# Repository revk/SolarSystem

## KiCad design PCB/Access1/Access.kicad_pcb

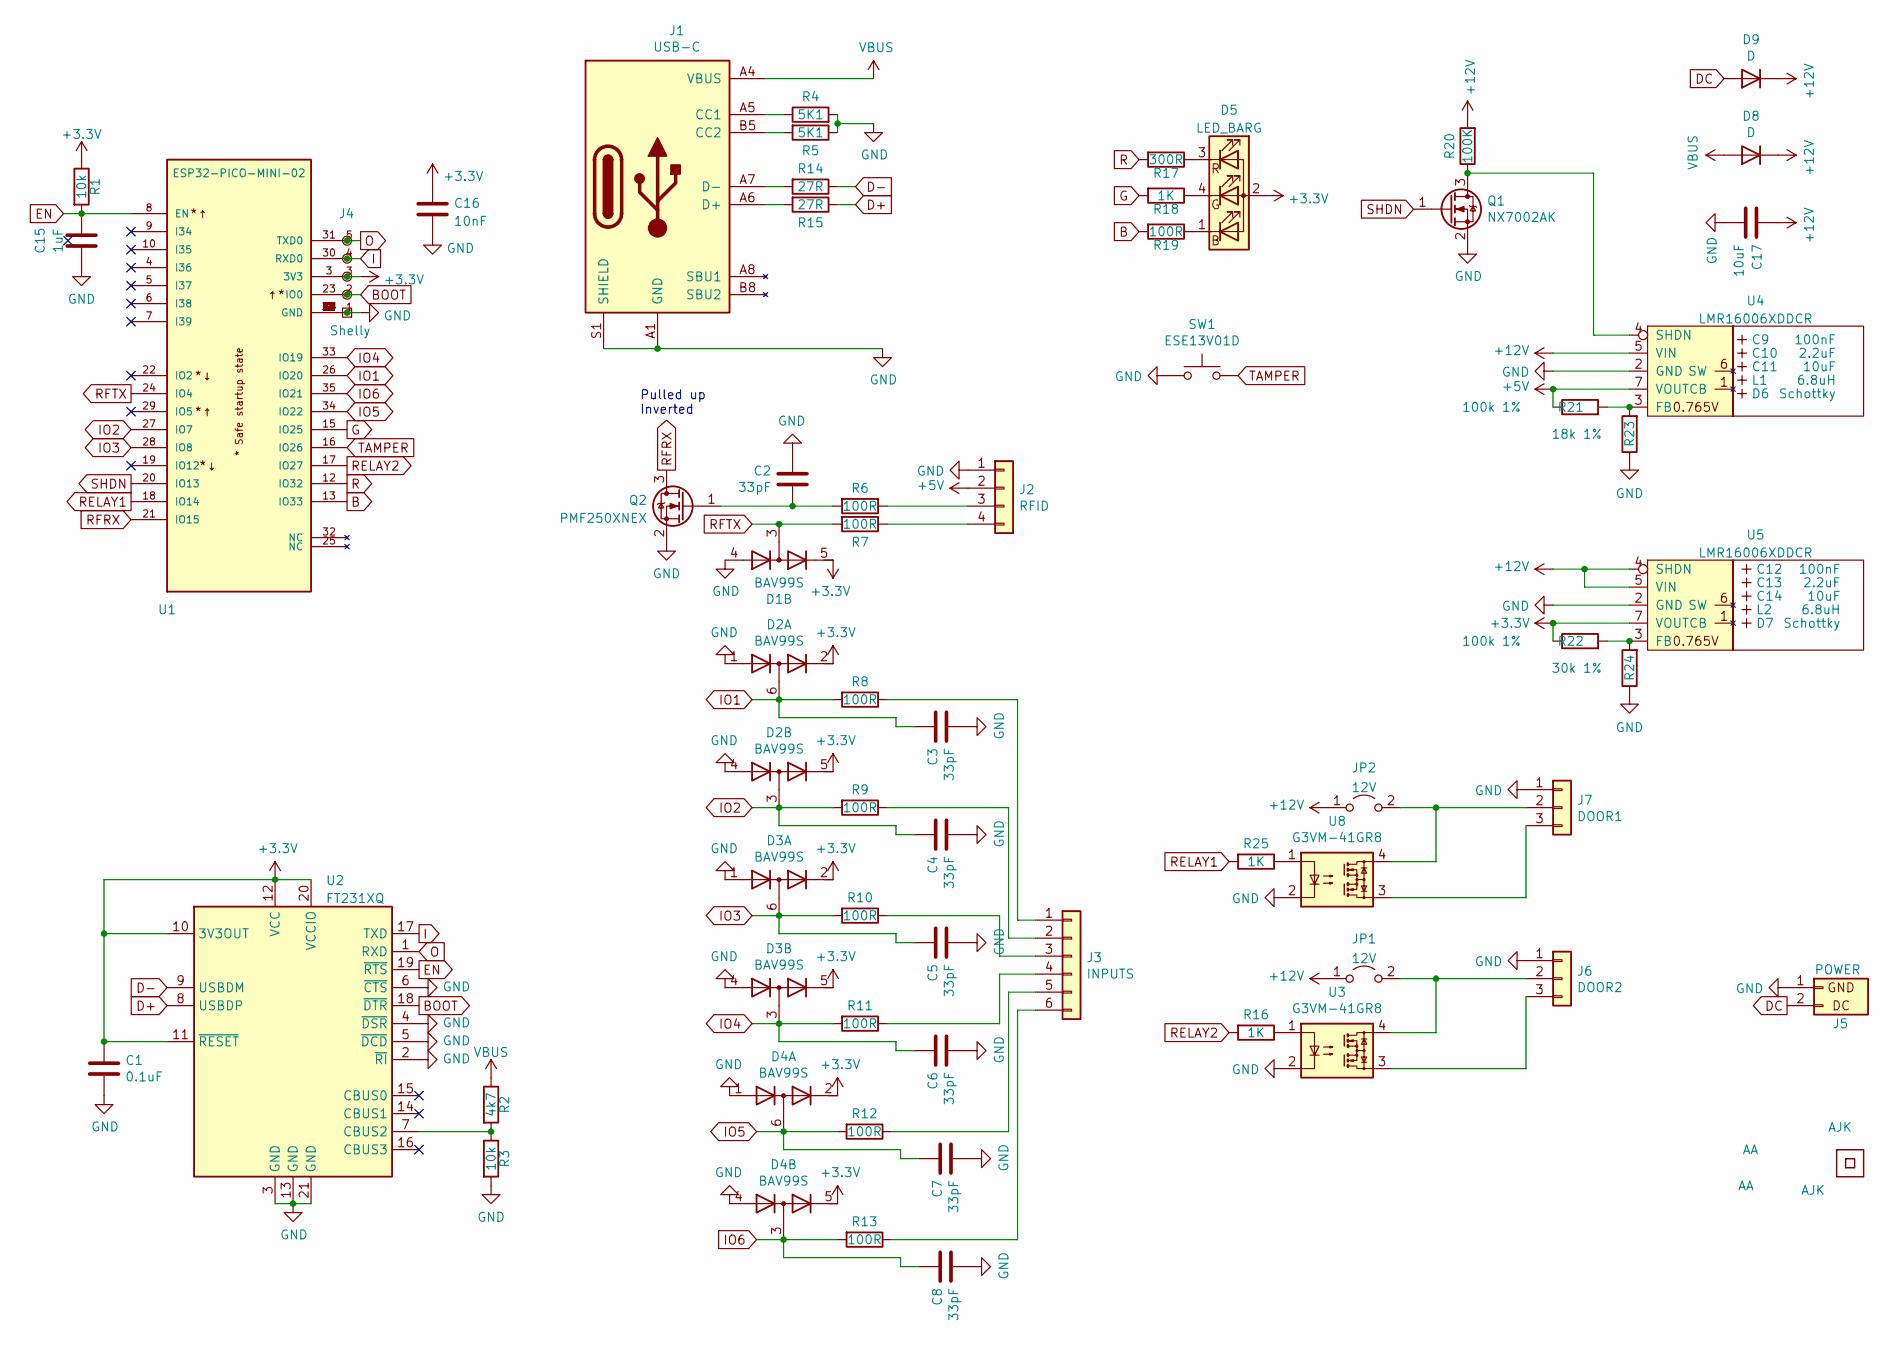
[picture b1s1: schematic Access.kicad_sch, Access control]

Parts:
AJK1: AJK
C1: 0.1uF; C_0603
C2, C3, C4, C5, C6, C7, C8: 33pF; C_0603
C9, C12: 100nF; C_0603_; LCSC Part # C30926
C10, C13: 2.2uF; C_0805_; LCSC Part # C19110
C11, C14: 10uF; C_0805_; LCSC Part # C17024
C15: 1uF; C_0603
C16: 10nF; C_0603
C17: 10uF; C_0805
D1, D2, D3, D4: BAV99S; SOT-363_SC-70-6; JLCPCB Rotation Offset 90
D5: LED_BARG; MHS190RGBCT; LCSC Part # C409798
D6, D7: Schottky; D_1206_; LCSC Part # C143805
D8, D9: D; D_1206; LCSC Part # C143805
J1: USB-C; USC16-TR; LCSC Part # C709357
J2: RFID; PTSM-HH-4-RA
J3: INPUTS; PTSM-HH-6-RA
J4: Shelly
J5: POWER; PTSM-HH1-2-RA
J6: DOOR2; PTSM-HH1-3-RA-W
J7: DOOR1; PTSM-HH1-3-RA
JP1, JP2: 12V; SolderJumper-2_P1.3mm_Open_RoundedPad1.0x1.5mm
L1, L2: 6.8uH; L_4x4_; LCSC Part # C354575
Logo1: AJK
Q1: NX7002AK; SOT-23; Part No NX7002AK; JLCPCB Rotation Offset 180
Q2: PMF250XNEX; SOT-323_SC-70; Part No PMF250XNEX; LCSC Part # C504047
R1, R3: 10k; R_0603
R2: 4k7; R_0603
R4, R5: 5K1; R_0603
R6, R7, R8, R9, R10, R11, R12, R13: 100R; R_0603
R14, R15: 27R; R_0603
R16, R25: 1K; R_0603
R17: 300R; R_0603; Part No 0603-680R
R18: 1K; R_0603; Part No 0603-2K
R19: 100R; R_0603; Part No 0603-220R
R20: 100K; R_0603
R21, R22: 100k 1%; R_0603; LCSC Part # C14675
R23: 18k 1%; R_0603; LCSC Part # C114610
R24: 30k 1%; R_0603; LCSC Part # C100001
SW1: ESE13V01D; ESE13
U1: ESP32-PICO-MINI-02; PARTREV v1.0; LCSC Part # C2980306
U2: FT231XQ; QFN-20-1EP_4x4mm_P0.5mm_EP2.5x2.5mm; JLCPCB Rotation Offset -90
U3, U8: G3VM-41GR8; Special-SOP-4-3.7x4.55; LCSC Part # C2691601
U4, U5: LMR16006XDDCR; SOT-23-Thin-6-Reg; Part No LMR16006XDDCR; LCSC Part # C87080
U6, U9: AA
U7: QR; QR-SS

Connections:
+3.3V: C1.1, C16.1, D1.5 (K4), D2.2 (K2), D2.5 (K4), D3.2 (K2), D3.5 (K4), D4.2 (K2), D4.5 (K4), D5.2 (A), J4.3 (3V3), R1.1, R22.1, U1.3 (3V3), U2.10 (3V3OUT), U2.11 (~RESET), U2.12 (VCC), U2.20 (VCCIO), U5.7 (VOUT)
+5V: J2.2, R21.1, U4.7 (VOUT)
+12V: C17.1, D8.1 (K), D9.1 (K), JP1.1 (A), JP2.1 (A), R20.2, U4.5 (VIN), U5.4 (SHDN), U5.5 (VIN)
B: R19.2, U1.13 (IO33)
BOOT: J4.2 (0), U1.23 (IO0), U2.18 (~DTR)
D+: R15.1, U2.8 (USBDP)
D-: R14.1, U2.9 (USBDM)
DC: D9.2 (A), J5.2 (DC)
EN: C15.2, R1.2, U1.8 (EN), U2.19 (~RTS)
G: R18.2, U1.15 (IO25)
GND: C1.2, C2.1, C3.2, C4.2, C5.2, C6.2, C7.2, C8.2, C15.1, C16.2, C17.2, D1.4 (A3), D2.1 (A1), D2.4 (A3), D3.1 (A1), D3.4 (A3), D4.1 (A1), D4.4 (A3), J1.A1 (GND), J1.A12 (GND), J1.B1 (GND), J1.B12 (GND), J1.S1 (SHIELD), J2.1, J4.1 (GND), J5.1 (GND), J6.1, J7.1, Q1.2 (S), Q2.2 (S), R3.2, R4.2, R5.1, R23.1, R24.1, SW1.1, U1.1 (GND), U1.2 (GND), U1.11 (GND), U1.14 (GND), U1.36 (GND), U1.37 (GND), U1.38 (GND), U1.39 (GND), U1.40 (GND), U1.41 (GND), U1.42 (GND), U1.43 (GND), U1.44 (GND), U1.45 (GND), U1.46 (GND), U1.47 (GND), U1.48 (GND), U1.49 (GND), U1.50 (GND), U1.51 (GND), U1.52 (GND), U1.53 (GND), U2.2 (~RI), U2.3 (GND), U2.4 (~DSR), U2.5 (~DCD), U2.6 (~CTS), U2.13 (GND), U2.21 (GND), U3.2, U4.2 (GND), U5.2 (GND), U8.2
I: J4.4 (Rx), U1.30 (RXD0), U2.17 (TXD)
IO1: C3.1, D2.6 (K3A4), R8.2, U1.26 (IO20)
IO2: C4.1, D2.3 (K1A2), R9.2, U1.27 (IO7)
IO3: C5.1, D3.6 (K3A4), R10.2, U1.28 (IO8)
IO4: C6.1, D3.3 (K1A2), R11.2, U1.33 (IO19)
IO5: C7.1, D4.6 (K3A4), R12.2, U1.34 (IO22)
IO6: C8.1, D4.3 (K1A2), R13.2, U1.35 (IO21)
unnamed: D5.1 (BK), R19.1
unnamed: D5.4 (GK), R18.1
unnamed: D5.3 (RK), R17.1
unnamed: J1.A5 (CC1), R4.1
unnamed: J1.B5 (CC2), R5.2
unnamed: J1.A6 (D+), J1.B6 (D+), R15.2
unnamed: J1.A7 (D-), J1.B7 (D-), R14.2
unnamed: J2.3, R6.1
unnamed: J2.4, R7.1
unnamed: J3.1, R8.1
unnamed: J3.2, R9.1
unnamed: J3.3, R10.1
unnamed: J3.4, R11.1
unnamed: J3.5, R12.1
unnamed: J3.6, R13.1
unnamed: J6.2, JP1.2 (B), U3.4
unnamed: J6.3, U3.3
unnamed: J7.2, JP2.2 (B), U8.4
unnamed: J7.3, U8.3
unnamed: Q1.3 (D), R20.1, U4.4 (SHDN)
unnamed: C2.2, Q2.1 (G), R6.2
unnamed: R16.1, U3.1
unnamed: R25.1, U8.1
unnamed: R2.2, R3.1, U2.7 (CBUS2)
unnamed: R21.2, R23.2, U4.3 (FB)
unnamed: R22.2, R24.2, U5.3 (FB)
O: J4.5 (Tx), U1.31 (TXD0), U2.1 (RXD)
R: R17.2, U1.12 (IO32)
RELAY1: R25.2, U1.18 (IO14)
RELAY2: R16.2, U1.17 (IO27)
RFRX: Q2.3 (D), U1.21 (IO15)
RFTX: D1.3 (K1A2), R7.2, U1.24 (IO4)
SHDN: Q1.1 (G), U1.20 (IO13)
TAMPER: SW1.2, U1.16 (IO26)
VBUS: D8.2 (A), J1.A4 (VBUS), J1.A9 (VBUS), J1.B4 (VBUS), J1.B9 (VBUS), R2.1

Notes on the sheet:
Pulled up Inverted

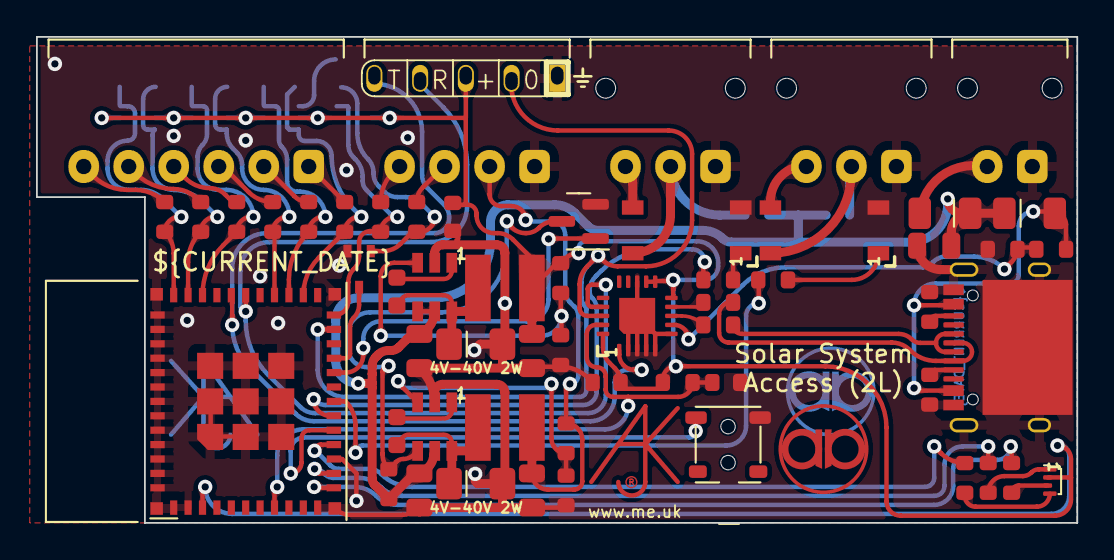
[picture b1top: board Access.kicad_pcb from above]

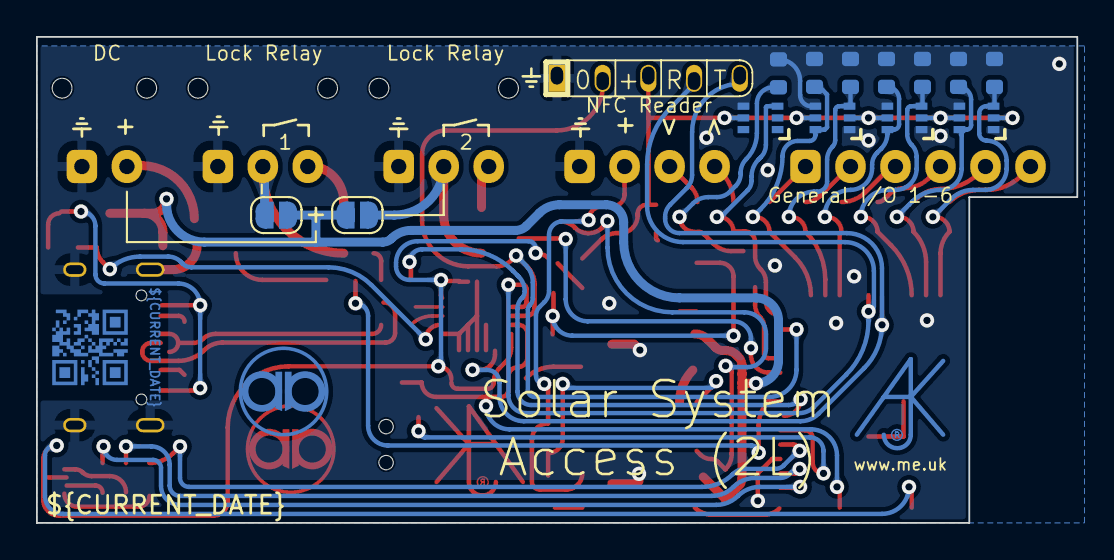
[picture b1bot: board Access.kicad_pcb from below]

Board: 2 copper layers, 57.8 x 27.0 mm, 76 parts (16 on the bottom side), 53 nets.

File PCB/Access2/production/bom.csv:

Designator,Footprint,Quantity,Value,LCSC Part #
C1,C_0603,1,0.1uF,
"C10, C13",C_0805_,2,2.2uF,C19110
"C11, C14",C_0805_,2,10uF,C17024
"C12, C9",C_0603_,2,100nF,C30926
"C15, C16",C_0603,2,10nF,
C17,C_0805,1,10uF,
"C2, C3, C4, C5, C6, C7, C8",C_0603,7,33pF,
"D1, D2, D3, D4",SOT-363_SC-70-6,4,BAV99S,
D5,MHS190RGBCT,1,LED_BARG,C409798
"D6, D7",D_1206_,2,Schottky,C143805
"D8, D9",D_1206,2,D,C143805
J1,USC16-TR,1,USB-C,C709357
J2,PTSM-HH-4-RA,1,RFID,
J3,PTSM-HH-6-RA,1,INPUTS,
J5,PTSM-HH1-2-RA,1,POWER,
J6,PTSM-HH1-3-RA,1,DOOR,
"L1, L2",L_4x4_,2,6.8uH,C354575
Q1,SOT-23,1,NX7002AK,
Q2,SOT-323_SC-70,1,PMF250XNEX,C504047
"R1, R3",R_0603,2,10k,
"R10, R11, R12, R13, R19, R6, R7, R8, R9",R_0603,9,100R,
"R14, R15",R_0603,2,27R,
"R16, R18",R_0603,2,1K,
R17,R_0603,1,300R,
R2,R_0603,1,4k7,
R20,R_0603,1,100K,
"R21, R22",R_0603,2,100k 1%,C14675
R23,R_0603,1,18k 1%,C114610
R24,R_0603,1,30k 1%,C100001
"R4, R5",R_0603,2,5K1,
SW1,ESE13,1,ESE13V01D,
U1,ESP32-PICO-MINI-02,1,ESP32-PICO-MINI-02,C2980306
U2,QFN-20-1EP_4x4mm_P0.5mm_EP2.5x2.5mm,1,FT231XQ,
U3,Special-SOP-4-3.7x4.55,1,G3VM-41GR8,C2691601
"U4, U5",SOT-23-Thin-6-Reg,2,LMR16006XDDCR,C87080

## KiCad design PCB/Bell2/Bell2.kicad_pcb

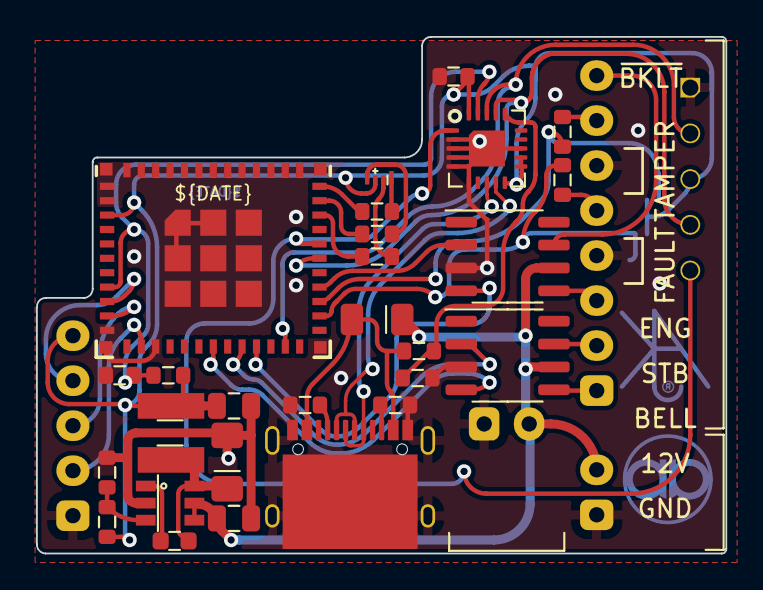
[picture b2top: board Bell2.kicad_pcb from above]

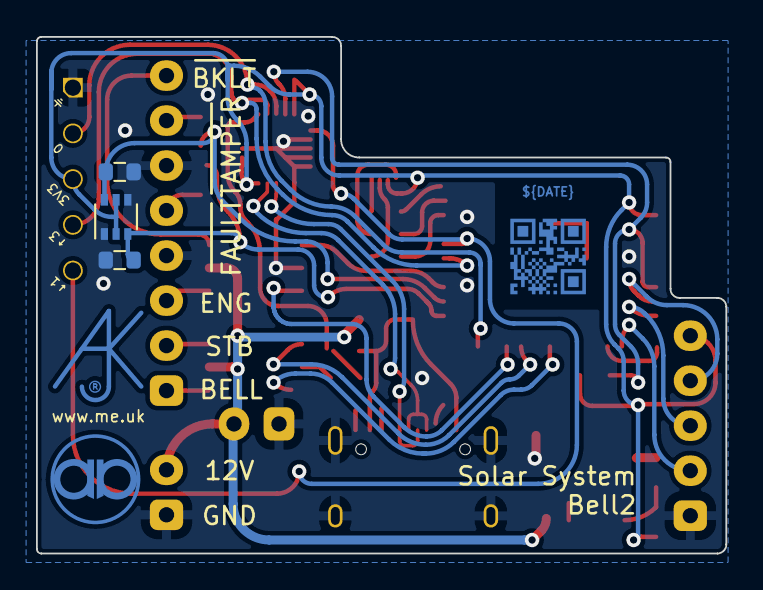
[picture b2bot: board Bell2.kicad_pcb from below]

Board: 2 copper layers, 38.3 x 28.7 mm, 38 parts (8 on the bottom side), 35 nets.

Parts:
AJK1: AJK
C1: 0.1uF; C_0603
C2, C3: 33pF; C_0603
C4: 100nF; C_0603_
C5: 2.2uF; C_0805_
C6: 10uF; C_0805_
C7: 10nF; C_0603
D1: BAV99S; SOT-363_SC-70-6
D2: LED_BARG; MHS190RGBCT
D3: D; D_1206
D4: Schottky; D_1206_
J1: USB-C; USC16-TR
J2: POWER; PTSM-HH-2-RA
J3: Conn_01x08; PTSM-HH-8-RA
J4: Shelly
J5: Conn_01x05; PTSM-HH-5-RA
J6: Conn_01x02; PTSM-HH-2-RA
L1: 6.8uH; L_4x4_
R1, R3: 10k; R_0603
R2: 4k7; R_0603
R4, R7, R10: 100R; R_0603
R5, R6: 5K1; R_0603
R8: 300R; R_0603
R9: 1K; R_0603
R11: 100k 1%; R_0603
R12: 30k 1%; R_0603
U1: ESP32-PICO-MINI-02
U2: FT231XQ; QFN-20-1EP_4x4mm_P0.5mm_EP2.5x2.5mm
U3, U4: ISL89410; SO-8_3.9x4.9mm_P1.27mm
U5: LMR16006XDDCR; SOT-23-Thin-6-Reg
U7: AA
U8: QR; QR-SS

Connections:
+3V3: C1.1, D1.2 (K2), D1.5 (K4), D2.2 (A), J4.3 (3V3), J5.5, R1.2, R11.1, U1.3 (3V3), U2.10 (3V3OUT), U2.11 (~RESET), U2.12 (VCC), U2.20 (VCCIO), U5.7 (VOUT)
+12V: D3.1 (K), J2.2 (DC), J6.2, U3.6 (V+), U4.6 (V+), U5.4 (SHDN), U5.5 (VIN)
B: R10.2, U1.34 (IO22)
BELL: J3.1, U3.5 (OUT_B)
BOOT: J4.2 (0), U1.23 (IO0), U2.18 (~DTR)
D+: J1.A6 (D+), J1.B6 (D+), U2.8 (USBDP)
D-: J1.A7 (D-), J1.B7 (D-), U2.9 (USBDM)
EN: C7.2, R1.1, U1.8 (EN), U2.19 (~RTS)
ENGHOLD: J3.3, U4.5 (OUT_B)
FAULT: J3.5, R7.1
G: R9.2, U1.35 (IO21)
GND: C1.2, C2.2, C3.2, C7.1, D1.1 (A1), D1.4 (A3), J1.A1 (GND), J1.A12 (GND), J1.B1 (GND), J1.B12 (GND), J1.S1 (SHIELD), J2.1 (GND), J3.4, J3.6, J4.1 (GND), J5.1, J6.1, R3.2, R5.2, R6.1, R12.1, U1.1 (GND), U1.2 (GND), U1.11 (GND), U1.14 (GND), U1.36 (GND), U1.37 (GND), U1.38 (GND), U1.39 (GND), U1.40 (GND), U1.41 (GND), U1.42 (GND), U1.43 (GND), U1.44 (GND), U1.45 (GND), U1.46 (GND), U1.47 (GND), U1.48 (GND), U1.49 (GND), U1.50 (GND), U1.51 (GND), U1.52 (GND), U1.53 (GND), U2.2 (~RI), U2.3 (GND), U2.4 (~DSR), U2.5 (~DCD), U2.6 (~CTS), U2.13 (GND), U2.21 (GND), U3.3 (GND), U4.3 (GND), U5.2 (GND)
GPSRX: J5.2, U1.13 (IO33)
GPSTICK: J5.4, U1.9 (I34)
GPSTX: J5.3, U1.10 (I35)
I: J4.4 (Rx), U1.30 (RXD0), U2.17 (TXD)
IN1: C2.1, D1.6 (K3A4), R4.2, U1.27 (IO7)
IN2: C3.1, D1.3 (K1A2), R7.2, U1.26 (IO20)
unnamed: D2.1 (BK), R10.1
unnamed: D2.3 (RK), R8.1
unnamed: D2.4 (GK), R9.1
unnamed: J1.A5 (CC1), R5.1
unnamed: J1.B5 (CC2), R6.2
unnamed: R2.2, R3.1, U2.16 (CBUS3)
unnamed: R11.2, R12.2, U5.3 (FB)
O: J4.5 (Tx), U1.31 (TXD0), U2.1 (RXD)
OUT1: U1.18 (IO14), U3.4 (IN_B)
OUT2: U1.20 (IO13), U3.2 (IN_A)
OUT3: U1.21 (IO15), U4.4 (IN_B)
OUT4: U1.28 (IO8), U4.2 (IN_A)
R: R8.2, U1.33 (IO19)
STB: J3.2, U3.7 (OUT_A)
T: J3.7, R4.1
VBUS: D3.2 (A), J1.A4 (VBUS), J1.A9 (VBUS), J1.B4 (VBUS), J1.B9 (VBUS), R2.1
~BACKLIGHT: J3.8, U4.7 (OUT_A)

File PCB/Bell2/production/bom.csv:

Designator,Footprint,Quantity,Value,LCSC Part #
C1,C_0603,1,0.1uF,
"C2, C3",C_0603,2,33pF,
C4,C_0603_,1,100nF,C30926
C5,C_0805_,1,2.2uF,C19110
C6,C_0805_,1,10uF,C17024
C7,C_0603,1,10nF,
D1,SOT-363_SC-70-6,1,BAV99S,
D2,LED-RGB-1.6x1.6,1,LED_RGBA,
D3,D_1206,1,D,
D4,D_1206_,1,Schottky,C143805
J1,USC16-TR,1,USB-C,
J2,PTSM-HH-2-RA,1,POWER,
J3,PTSM-HH-8-RA,1,Conn_01x08,
J5,PTSM-HH-5-RA,1,Conn_01x05,
J6,PTSM-HH-2-RA,1,Conn_01x02,
L1,L_4x4_,1,6.8uH,C354575
"R1, R3",R_0603,2,10k,
R10,R_0603,1,220R,
R11,R_0603,1,100k 1%,C14675
R12,R_0603,1,30k 1%,C100001
R2,R_0603,1,4k7,
"R4, R7",R_0603,2,100R,
"R5, R6",R_0603,2,5K1,
R8,R_0603,1,680R,
R9,R_0603,1,2K,
U1,ESP32-PICO-MINI-02,1,ESP32-PICO-MINI-02,
U2,QFN-20-1EP_4x4mm_P0.5mm_EP2.5x2.5mm,1,FT231XQ,
"U3, U4",SO-8_3.9x4.9mm_P1.27mm,2,ISL89410,
U5,SOT-23-Thin-6-Reg,1,LMR16006XDDCR,C87080

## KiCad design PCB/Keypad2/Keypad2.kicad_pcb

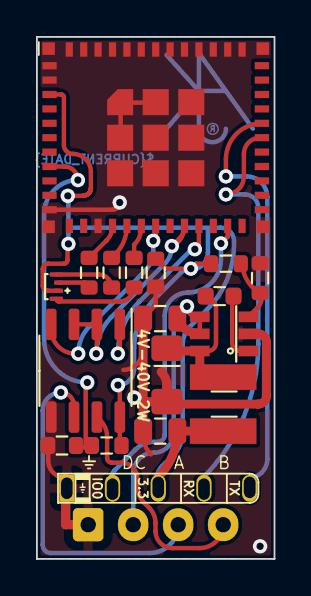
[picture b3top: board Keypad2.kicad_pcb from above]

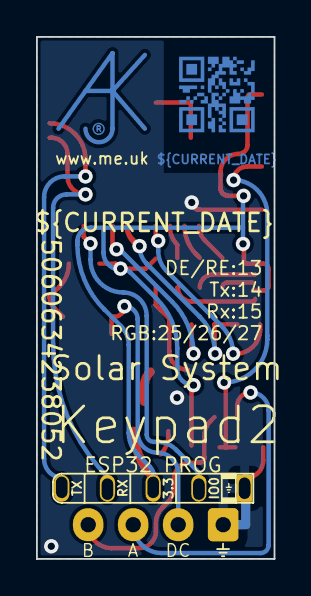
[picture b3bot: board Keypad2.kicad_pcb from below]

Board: 2 copper layers, 13.2 x 29.0 mm, 21 parts (3 on the bottom side), 19 nets.

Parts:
C1: 1uF; C_0603
C2: 100nF; C_0603_
C3: 2.2uF; C_0805_
C4: 10uF; C_0805_
C5: 100nF; C_0603
D1: Schottky; D_1206_
D2: LED_BARG; MHS190RGBCT
J1: Keypad; Molex_MiniSPOX_H4V
J2: Shelly
L1: 6.8uH; L_4x4_
Logo1: AJK
R1: 10K; R_0603
R2: 680R; R_0603
R3: 2K; R_0603
R4: 220R; R_0603
R7: 100k 1%; R_0603
R8: 30k 1%; R_0603
U1: SP3485; SO-8_3.9x4.9mm_P1.27mm
U2: ESP32-PICO-MINI-02
U3: LMR16006YDDCR; SOT-23-Thin-6-Reg
U4: QR; QR-SS

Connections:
+3V3: C5.1, D2.2 (A), J2.3 (3V3), R1.1, R7.1, U1.8 (Vcc), U2.3 (3V3), U3.7 (VOUT)
+12V: J1.2, U3.4 (SHDN), U3.5 (VIN)
B: R4.2, U2.17 (IO27)
DE: U1.2 (RE), U1.3 (DE), U2.20 (IO13)
G: R3.2, U2.16 (IO26)
GND: C1.1, C5.2, J1.1, J2.1 (GND), R8.1, U1.5 (GND), U2.1 (GND), U2.2 (GND), U2.11 (GND), U2.14 (GND), U2.36 (GND), U2.37 (GND), U2.38 (GND), U2.39 (GND), U2.40 (GND), U2.41 (GND), U2.42 (GND), U2.43 (GND), U2.44 (GND), U2.45 (GND), U2.46 (GND), U2.47 (GND), U2.48 (GND), U2.49 (GND), U2.50 (GND), U2.51 (GND), U2.52 (GND), U2.53 (GND), U3.2 (GND)
GPIO0: J2.2 (0), U2.23 (IO0)
I: J2.4 (Rx), U2.30 (RXD0)
unnamed: D2.1 (BK), R4.1
unnamed: D2.4 (GK), R3.1
unnamed: D2.3 (RK), R2.1
unnamed: J1.3, U1.6 (A)
unnamed: J1.4, U1.7 (B)
unnamed: C1.2, R1.2, U2.8 (EN)
unnamed: R7.2, R8.2, U3.3 (FB)
O: J2.5 (Tx), U2.31 (TXD0)
R: R2.2, U2.15 (IO25)
RX: U1.1 (RO), U2.21 (IO15)
TX: U1.4 (DI), U2.18 (IO14)

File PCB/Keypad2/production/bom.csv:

Designator,Footprint,Quantity,Value,LCSC Part #
C1,C_0603,1,10nF,
C2,C_0603_,1,100nF,C30926
C3,C_0805_,1,2.2uF,C19110
C4,C_0805_,1,10uF,C17024
C5,C_0603,1,100nF,
D1,D_1206_,1,Schottky,C143805
D2,MHS190RGBCT,1,LED_BARG,C409798
J1,Molex_MiniSPOX_H4V,1,Keypad,
L1,L_4x4_,1,6.8uH,C354575
R1,R_0603,1,10K,
R2,R_0603,1,680R,
R3,R_0603,1,2K,
R4,R_0603,1,220R,
R7,R_0603,1,100k 1%,C14675
R8,R_0603,1,30k 1%,C100001
U1,SO-8_3.9x4.9mm_P1.27mm,1,SP3485,
U2,ESP32-PICO-MINI-02,1,ESP32-PICO-MINI-02,
U3,SOT-23-Thin-6-Reg,1,LMR16006YDDCR,C290195

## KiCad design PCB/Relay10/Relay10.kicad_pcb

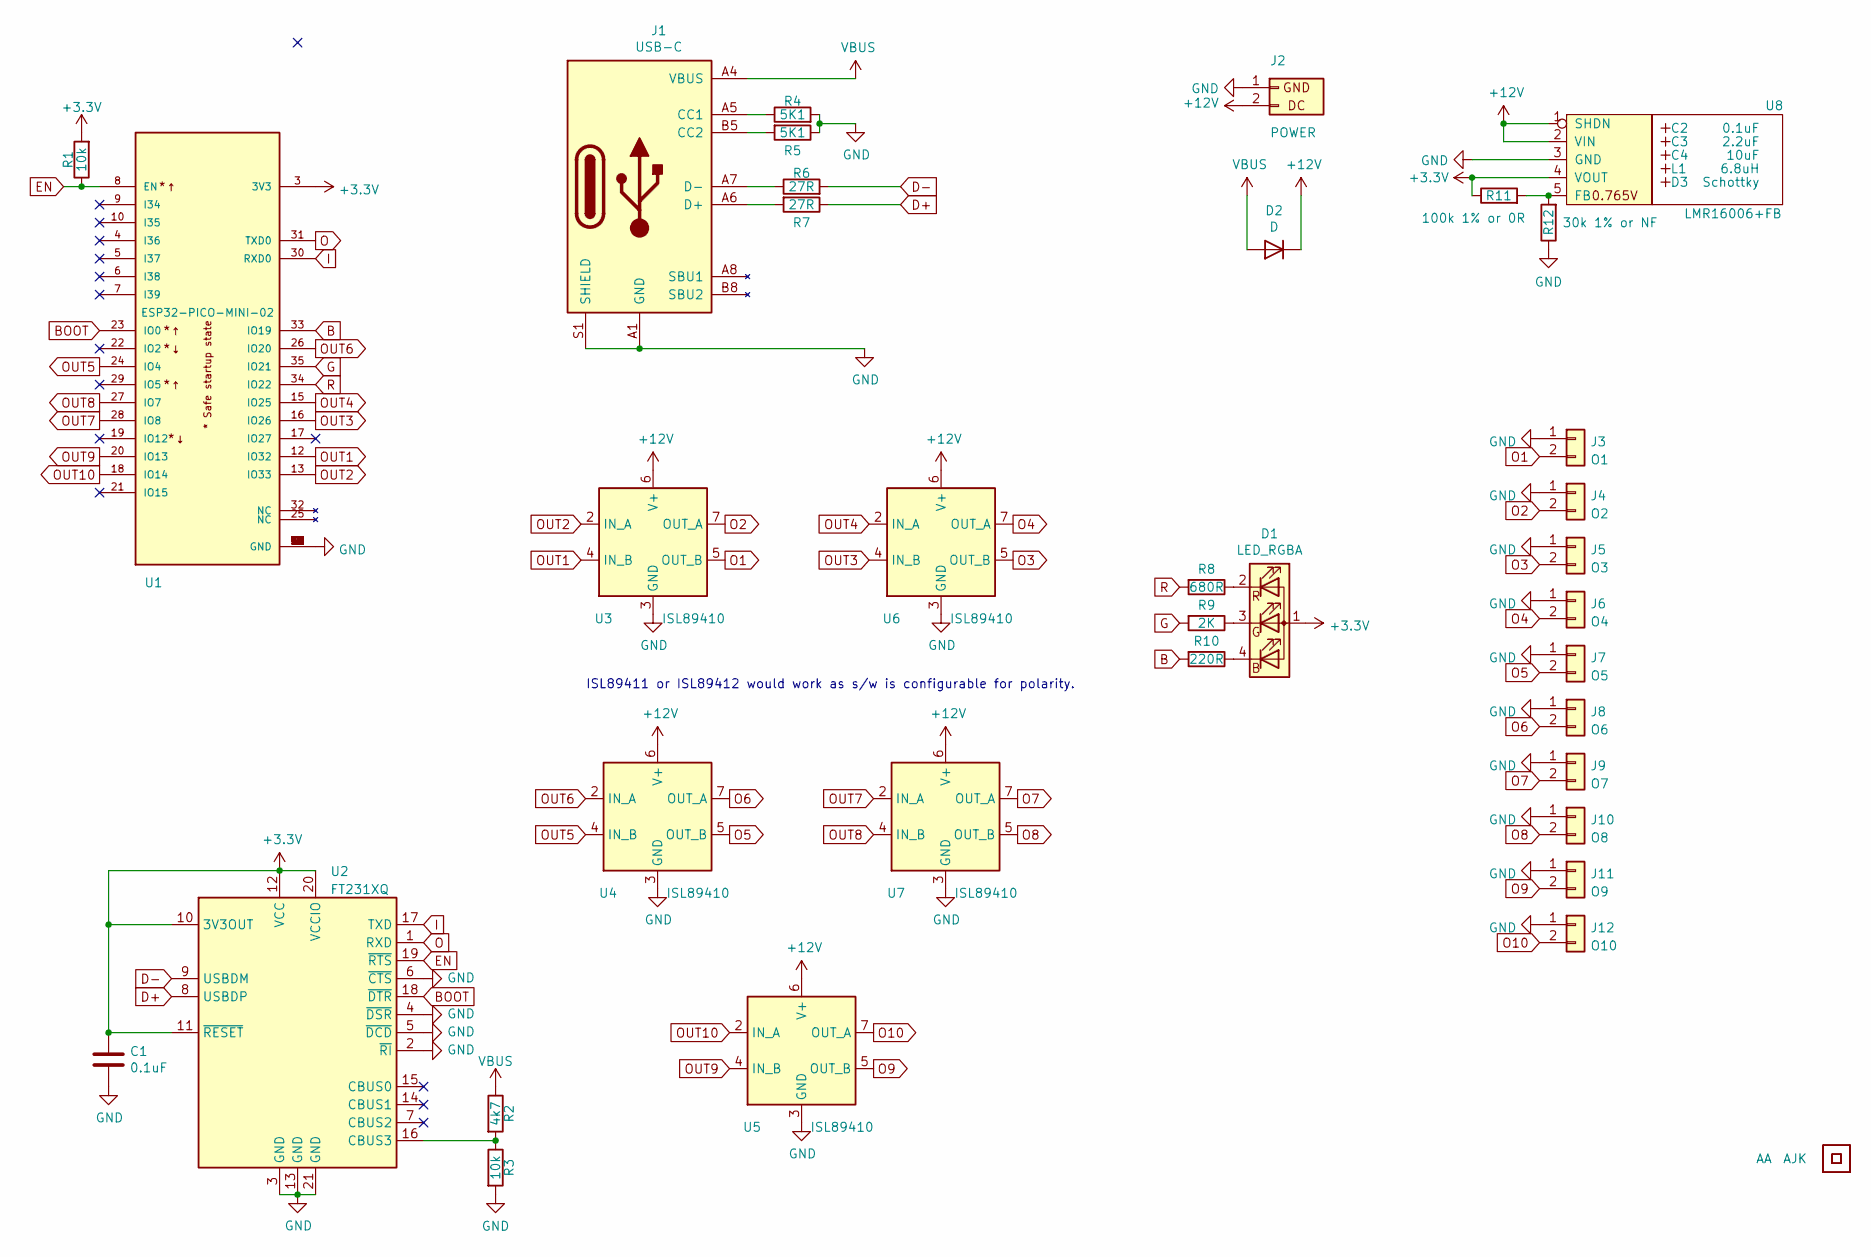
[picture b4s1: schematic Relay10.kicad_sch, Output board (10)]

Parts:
AJK1: AJK
C1: 0.1uF; C_0603
C2: 0.1uF; Hidden
C3: 2.2uF; Hidden
C4: 10uF; Hidden
D1: LED_RGBA; LED-RGB-1.6x1.6
D2: D; D_1206
D3: Schottky; Hidden; Part No CD1206-B2100
J1: USB-C; USC16-TR-Round
J2: POWER; Molex_MiniSPOX_H2RA
J3: O1; Molex_MiniSPOX_H2RA
J4: O2; Molex_MiniSPOX_H2RA
J5: O3; Molex_MiniSPOX_H2RA
J6: O4; Molex_MiniSPOX_H2RA
J7: O5; Molex_MiniSPOX_H2RA
J8: O6; Molex_MiniSPOX_H2RA
J9: O7; Molex_MiniSPOX_H2RA
J10: O8; Molex_MiniSPOX_H2RA
J11: O9; Molex_MiniSPOX_H2RA
J12: O10; Molex_MiniSPOX_H2RA
L1: 6.8uH; Hidden; Part No TYA4020
R1, R3: 10k; R_0603
R2: 4k7; R_0603
R4, R5: 5K1; R_0603
R6, R7: 27R; R_0603
R8: 680R; R_0603
R9: 2K; R_0603
R10: 220R; R_0603
R11: 100k 1% or 0R; R_0603
R12: 30k 1% or NF; R_0603
U1: ESP32-PICO-MINI-02; PARTREV v1.0
U2: FT231XQ; QFN-20-1EP_4x4mm_P0.5mm_EP2.5x2.5mm
U3, U4, U5, U6, U7: ISL89410; SO-8_3.9x4.9mm_P1.27mm
U8: LMR16006+FB; RegulatorBlockFB; Part No LMR16006YQ3
U9: AA
U10: QR; QR-SS

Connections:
+3V3: C1.1, D1.1 (A), R1.2, R11.1, U1.3 (3V3), U2.10 (3V3OUT), U2.11 (~RESET), U2.12 (VCC), U2.20 (VCCIO), U8.4 (VOUT)
+12V: D2.1 (K), J2.2 (DC), U3.6 (V+), U4.6 (V+), U5.6 (V+), U6.6 (V+), U7.6 (V+), U8.1 (SHDN), U8.2 (VIN)
B: R10.2, U1.33 (IO19)
BOOT: U1.23 (IO0), U2.18 (~DTR)
D+: R7.1, U2.8 (USBDP)
D-: R6.2, U2.9 (USBDM)
EN: R1.1, U1.8 (EN), U2.19 (~RTS)
G: R9.2, U1.35 (IO21)
GND: C1.2, J1.A1 (GND), J1.A12 (GND), J1.B1 (GND), J1.B12 (GND), J1.S1 (SHIELD), J2.1 (GND), J3.1, J4.1, J5.1, J6.1, J7.1, J8.1, J9.1, J10.1, J11.1, J12.1, R3.2, R4.2, R5.1, R12.1, U1.1 (GND), U1.2 (GND), U1.11 (GND), U1.14 (GND), U1.36 (GND), U1.37 (GND), U1.38 (GND), U1.39 (GND), U1.40 (GND), U1.41 (GND), U1.42 (GND), U1.43 (GND), U1.44 (GND), U1.45 (GND), U1.46 (GND), U1.47 (GND), U1.48 (GND), U1.49 (GND), U1.50 (GND), U1.51 (GND), U1.52 (GND), U1.53 (GND), U2.2 (~RI), U2.3 (GND), U2.4 (~DSR), U2.5 (~DCD), U2.6 (~CTS), U2.13 (GND), U2.21 (GND), U3.3 (GND), U4.3 (GND), U5.3 (GND), U6.3 (GND), U7.3 (GND), U8.3 (GND)
I: U1.30 (RXD0), U2.17 (TXD)
unnamed: D1.2 (RK), R8.1
unnamed: D1.3 (GK), R9.1
unnamed: D1.4 (BK), R10.1
unnamed: J1.A5 (CC1), R4.1
unnamed: J1.A6 (D+), J1.B6 (D+), R7.2
unnamed: J1.A7 (D-), J1.B7 (D-), R6.1
unnamed: J1.B5 (CC2), R5.2
unnamed: R2.2, R3.1, U2.16 (CBUS3)
unnamed: R11.2, R12.2, U8.5 (FB)
O: U1.31 (TXD0), U2.1 (RXD)
O1: J3.2, U3.5 (OUT_B)
O2: J4.2, U3.7 (OUT_A)
O3: J5.2, U6.5 (OUT_B)
O4: J6.2, U6.7 (OUT_A)
O5: J7.2, U4.5 (OUT_B)
O6: J8.2, U4.7 (OUT_A)
O7: J9.2, U7.7 (OUT_A)
O8: J10.2, U7.5 (OUT_B)
O9: J11.2, U5.5 (OUT_B)
O10: J12.2, U5.7 (OUT_A)
OUT1: U1.12 (IO32), U3.4 (IN_B)
OUT2: U1.13 (IO33), U3.2 (IN_A)
OUT3: U1.16 (IO26), U6.4 (IN_B)
OUT4: U1.15 (IO25), U6.2 (IN_A)
OUT5: U1.24 (IO4), U4.4 (IN_B)
OUT6: U1.26 (IO20), U4.2 (IN_A)
OUT7: U1.28 (IO8), U7.2 (IN_A)
OUT8: U1.27 (IO7), U7.4 (IN_B)
OUT9: U1.20 (IO13), U5.4 (IN_B)
OUT10: U1.18 (IO14), U5.2 (IN_A)
R: R8.2, U1.34 (IO22)
VBUS: D2.2 (A), J1.A4 (VBUS), J1.A9 (VBUS), J1.B4 (VBUS), J1.B9 (VBUS), R2.1

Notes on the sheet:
ISL89411 or ISL89412 would work as s/w is configurable for polarity.

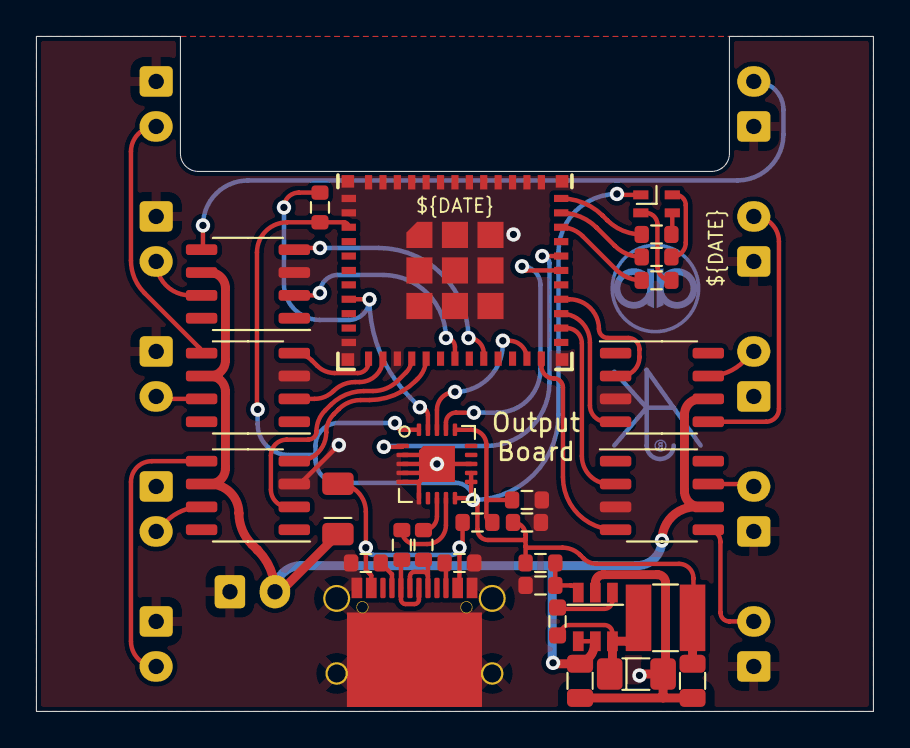
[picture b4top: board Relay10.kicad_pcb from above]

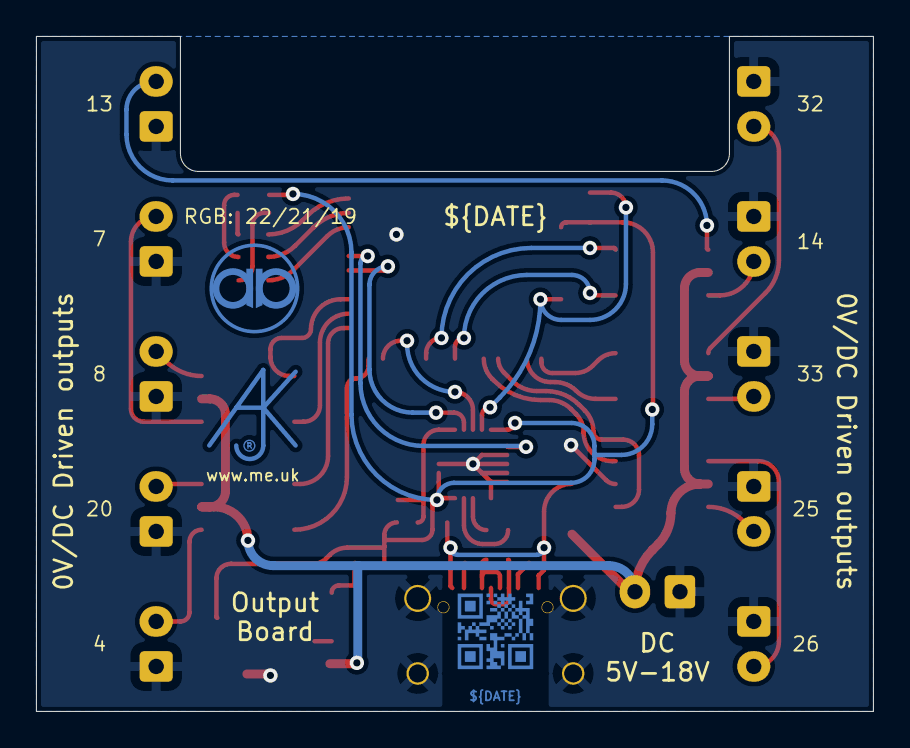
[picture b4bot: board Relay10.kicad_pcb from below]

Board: 2 copper layers, 46.5 x 37.5 mm, 43 parts (3 on the bottom side), 42 nets.

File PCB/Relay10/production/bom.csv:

Designator,Footprint,Quantity,Value,LCSC Part #
AJK1,AJK,1,AJK,
C1,C_0603,1,0.1uF,
C2,Hidden,1,0.1uF,
C3,Hidden,1,2.2uF,
C4,Hidden,1,10uF,
D1,LED-RGB-1.6x1.6,1,LED_RGBA,
D2,D_1206,1,D,
D3,Hidden,1,Schottky,
J1,USC16-TR-Round,1,USB-C,
J10,Molex_MiniSPOX_H2RA,1,O8,
J11,Molex_MiniSPOX_H2RA,1,O9,
J12,Molex_MiniSPOX_H2RA,1,O10,
J2,Molex_MiniSPOX_H2RA,1,POWER,
J3,Molex_MiniSPOX_H2RA,1,O1,
J4,Molex_MiniSPOX_H2RA,1,O2,
J5,Molex_MiniSPOX_H2RA,1,O3,
J6,Molex_MiniSPOX_H2RA,1,O4,
J7,Molex_MiniSPOX_H2RA,1,O5,
J8,Molex_MiniSPOX_H2RA,1,O6,
J9,Molex_MiniSPOX_H2RA,1,O7,
L1,Hidden,1,6.8uH,
"R1, R3",R_0603,2,10k,
R10,R_0603,1,220R,
R11,R_0603,1,100k 1% or 0R,
R12,R_0603,1,30k 1% or NF,
R2,R_0603,1,4k7,
"R4, R5",R_0603,2,5K1,
"R6, R7",R_0603,2,27R,
R8,R_0603,1,680R,
R9,R_0603,1,2K,
U1,ESP32-PICO-MINI-02,1,ESP32-PICO-MINI-02,
U2,QFN-20-1EP_4x4mm_P0.5mm_EP2.5x2.5mm,1,FT231XQ,
"U3, U4, U5, U6, U7",SO-8_3.9x4.9mm_P1.27mm,5,ISL89410,
U8,RegulatorBlockFB,1,LMR16006+FB,
U9,AA,1,AA,
